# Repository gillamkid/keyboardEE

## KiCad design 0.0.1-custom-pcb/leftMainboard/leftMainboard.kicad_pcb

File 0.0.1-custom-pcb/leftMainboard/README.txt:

leftMainboard -- Glove80 LH controller, photograph reconstruction
KiCad 9 project, draft revision 1

OPEN
Open leftMainboard.kicad_pro in KiCad. Both an editable board and a four-sheet
schematic are included. Reconstruction.pretty and Reconstruction.kicad_sym
are project-local libraries. Your existing breakout projects were not edited.

STATUS AND SCOPE
This is a best-effort reconstruction of the photographed Rev J / 2022 board.
Component positions, four mounting holes, USB/GPIO/power/battery connectors,
FPC rows and the long matrix bus bundle follow the photos. Native F.Cu/B.Cu
routing represents the inferred netlist. Ambiguous paths were re-routed;
the native copper is an approximation, not a verified trace-for-trace clone.
Do not fabricate or energize this draft as a verified Glove80 replacement.

The photos do not establish all resistor/capacitor values, concealed connections,
board thickness/layer stack, every semiconductor MPN or connector polarity.
The power stage and LED interface require actual-board continuity checks and
identification of U1/Q1/Q2/Q3 before a working circuit can be claimed.
U1 BOOST_COMP and BOOST_SS are deliberately unresolved named terminals.
The final LED return IN40 is intentionally not connected to the processor.

LAYOUT GEOMETRY
Nominal size: 45 x 75 mm, estimated from known module dimensions and pitches.
Notch: approximately 7.5 x 25 mm. Holes: approximately 3 mm diameter.
Coordinates and dimensions were inferred from photos without a ruler; expect
roughly 0.5--1 mm placement/dimension uncertainty. Confirm the actual dimensions,
hole plating, screw clearance and enclosure fit before using the board mechanically.
Larger substitute footprints occasionally require small placement shifts.
The native routing uses 0.10 mm minimum clearance and some 0.10 mm escape tracks,
with 0.40/0.20 and 0.45/0.20 mm vias. These are reconstruction assumptions.
Some MCU escapes use vias in pads; the actual board's via process is unverified.
The rear ground fill and long front strap are photo-derived; additional top-side
ground areas and stitching connections are inferred to complete draft connectivity.

PHOTOGRAPH REFERENCES
references/Top.png: populated board, rectified to 30 pixels per mm.
references/TopSanded.png and BottomSanded.png: registered surface-copper photos.
The *-grid.png files add a 1 mm coordinate grid. Bottom images are registered
in the same top-view coordinate system as the KiCad PCB.
references/photo-registration.json records the homographies and mounting-hole landmarks.

User.1 (Photo top copper) and User.2 (Photo bottom copper) hold native graphical
copper-edge contours extracted from the photos. They are documentary graphics.
They do not represent electrical nets or contribute to fabrication copper.
Thresholding includes some sanding artifacts and misses obscured/shadowed copper;
the registered photographs retain the original evidence. Toggle these layers
individually to compare them against the editable F.Cu/B.Cu routing.
The battery envelope is on Dwgs.User; it is not an assembled PCB component.
Reference designators are on F.Fab to keep the densely packed silk uncluttered.

CONNECTORS -- REQUESTED USER PINOUTS
J7, 14 contacts, nearest the processor:
1 R0, 2 R1, 3 R2, 4 R3, 5 R4, 6 R5, 7 VDD, 8 GND,
9 IN16, 10 IN0, 11 C2, 12 C1, 13 C0, 14 NC. Anchors 15/16 NC.
J8, nearest 12-contact connector to J7:
1..6 R0..R5, 7 VDD, 8 GND, 9 IN22, 10 IN16, 11 C3, 12 NC.
J9, middle remaining 12-contact connector:
1..6 R0..R5, 7 VDD, 8 GND, 9 IN28, 10 IN22, 11 C4, 12 NC.
J10, farthest connector from J7:
1..6 R0..R5, 7 VDD, 8 GND, 9 IN40, 10 IN28, 11 C6, 12 C5.
All 12-contact mechanical anchors 13/14 are NC.
VDD denotes the external LED supply, estimated at 5 V, not the MCU 2.4 V rail.
FPC MPNs are substitutes from your breakout libraries, not identified factory parts.

FIRMWARE MAPPING -- CONFIRMED BY OFFICIAL DEVICE TREE
R0: P0.26
R1: P0.05
R2: P0.06
R3: P0.08
R4: P0.07
R5: P1.09
C0: P1.01
C1: P1.03
C2: P1.05
C3: P1.07
C4: P1.06
C5: P1.04
C6: P1.08
LED serial data: P0.27
LED power enable: P0.31
Rear status LED PWM: P1.15

The LH firmware array lists columns in the opposite order from your C0-at-thumb
numbering; the table above translates to your physical C0..C6 convention.
Each half has 40 LEDs. The inferred external chain follows 16 + 6 + 6 + 12 keys:
IN0 -> J7 breakout -> IN16 -> J8 -> IN22 -> J9 -> IN28 -> J10 -> IN40.

J3 GPIO/SWD header, 2 x 6, pitch 1.27 mm:
1 GND, 2 VEXT_2V4, 3 VDDH, 4 EXT1, 5 EXT2, 6 EXT3,
7 EXT4, 8 EXT5, 9 EXT6/SWO, 10 RESET, 11 SWDCLK, 12 SWDIO.
EXT1: P0.22
EXT2: P0.21
EXT3: P0.24
EXT4: P0.20
EXT5: P0.25
EXT6: P1.00
MoErgo documents VEXT as typically 2.4 V and VDDH as approximately 3--5 V.
RESET connects to module P0.18; SWDIO/SWDCLK use their dedicated module pads.

PARTS WITH THE STRONGEST EVIDENCE
U4: Raytac MDBT50Q nRF52840 module, PCB antenna variant; suffix P1MV2 inferred.
U2: TP4056 charger marking clearly visible; exact package/ordering suffix inferred.
U3: Nexperia PRTR5V0U2X USB protection, consistent with %R1 marking and SOT143.
L1: 330 marking supports 33 uH; current rating and exact MPN are unknown.
J3: official GPIO header and mapping, with photographed 1.27 mm pitch.

PARTS / DETAILS REQUIRING IDENTIFICATION OR MEASUREMENT
U1: unidentified eight-pin boost controller, marking resembles MXCEA/M1CEA.
The TPS61085-like functional pin map is only a provisional guess; no compatible
replacement or original pinout was established. Feedback/compensation/soft-start
and LED-enable behavior must be checked. Do not order U1 based on this guess.
U5: b25 marking suggests 74CBTLV1G125GV. That device is a 2.3--3.6 V bus switch;
it is not a generic 5 V buffer. The draft uses VEXT_2V4 for its supply, but the
photographed LED voltage-translation topology is unresolved.
Q1/Q3: N-channel MOSFETs supported by user diode measurements and SS marking;
BSS138 remains a candidate, with exact manufacturer/MPN unconfirmed.
Q2: user-selected TECH PUBLIC DMG2305UX, LCSC C2940629; P-channel confirmed by user multimeter test, 5PEY marking matches manufacturer 5Pxx format. Manually sized footprint pads retained.
D3/D4: likely Schottky diodes; BAT54WS and PMEG2010ER are estimates, not verified.
D5: status LED package/colour/current rating inferred.
F1: Bourns MF-NSMF150-2, LCSC C89655; 1.5 A hold, 3 A trip, 6 V, 1206 resettable fuse. Selected by user from the marking and measured package dimensions.
Y1: likely a 32.768 kHz crystal; load capacitance and exact package unverified.
L2/L3: ferrite/filter and 10 uH MCU power inductor estimates.
Every resistor/capacitor value, rating and package is inferred. Even apparently
standard 5.1k USB CC resistors should be confirmed on the actual board.
SW1: latching DPDT-style power switch; footprint and terminal assignment estimated.
SW2: user-selected SHOU HAN TS3735A 250gf 030, LCSC C2906282. Project-local EasyEDA footprint and STEP/VRML models. Common pairs 1/2 = RESET and 3/4 = GND; footprint rotated 90 degrees to preserve left/right net sides.
J1: generic 16-contact USB-C footprint; compare shell lands with the factory part.
J2: estimated 1.25 mm three-wire LiPo connector; verify family AND BATTERY POLARITY.
TP1..TP14: exposed small lands beside the column-filter components; their probing
function and inferred column/GND assignments are unconfirmed.
H1..H4: inferred plated holes, confirm whether the originals are plated.
See component-confidence.csv for the evidence and candidate for every footprint.

VALIDATION
review/ contains the final KiCad DRC and ERC reports, netlist export, board
previews and a schematic-to-PCB audit. Unresolved DRC findings are preserved.
The schematic symbols are evidence-capture symbols with passive electrical pins;
ERC cannot validate the assumed IC functions or prove that this circuit works.
Passing net/pin checks establishes consistency of the reconstruction only.

Evidence sources and the pinned firmware revision are in references/sources.txt.

FINAL CHECK RESULTS (KiCad 9.0.8, 2026-10-07)
300 physical pad instances checked against the inferred pin maps and schematic.
0 pin-map mismatches; 0 schematic/PCB parity issues; 0 unrouted connections.
8 DRC errors, all courtyard overlaps among estimated footprints.
20 DRC warnings: unused track/via ends remain in the reconstructed buses.
0 ERC errors; 4 singleton global-label warnings (IN40, BOOST_COMP, BOOST_SS, CHARGE_DONE).
The latter reflect an unused final LED return and unresolved/unused power-stage terminals.
Detailed counts and component pairs are in review/drc.rpt and schematic-pcb-audit.json.
These checks establish internal net consistency, not a verified working circuit.

PROJECT-LOCAL 3D MODELS
All 60 fitted component footprints now have local 3D models under 3dmodels/.
Model assignments are updated in the PCB and Reconstruction.pretty library.
SW1, SW2 and L1 now use project-local EasyEDA models for their selected parts;
J2 and Y1 use representative library models for the estimated package.
See 3dmodels/README.txt and review/3d-model-coverage.csv for provenance and limits.

EMBEDDED SANDED-BOARD PHOTOGRAPHS 20261007-185202
Actual full-color PNG photos are embedded directly in the PCB, at registered 45x75mm size. User.3: Sanded top photo. User.4: Sanded bottom photo (registered to the same top-view coordinates). Select one of these layers in the PCB Editor Appearance panel; show one photo at a time. User.1/User.2 remain the earlier copper contour references. Images are locked against accidental movement. Local view preferences show the top photo at full opacity and hide the other photo and contour layers. Board copper, pads, component placements, models and connections were preserved. See review/embedded-sanded-photos.json.

REFERENCE LAYER CLEANUP 20261007-213601
Removed Photo top copper (User.1) and Photo bottom copper (User.2) and their 6877 obsolete contour graphics from this PCB. Sanded top/bottom photos on User.3/User.4 remain embedded and locked. Photo centers realigned to [72.36667, 87.63333] mm, following the board translation [49.86667, 50.13333] mm measured from all four mounting holes. Earlier notes describing the contour layers and fixed origin are superseded. Existing copper, pads, holes, component positions and 3D models were preserved exactly.

L1 REPLACEMENT 20261008-135743
Left mainboard L1 now uses user-selected XRCD54-1R8M / LCSC C5339378, 1.8uH +/-20%, 4A, DCR 30mOhm max. This supersedes the former photo-estimated 33uH value. The schematic, PCB, local footprint and local symbol defaults have been updated; pin 1 remains VDDH and pin 2 BOOST_SW. Position is unchanged; the footprint angle is now 90 degrees to preserve the upper/lower net arrangement with EasyEDA native pad numbering. Source pad positions +/-2.33mm and sizes 3x5.5mm imported; body contour is F.Fab and a bounding courtyard enclosing pads has been added. Both STEP and colored VRML are stored inside this project; STEP is active. User explicitly requested leaving all tracks and vias unchanged, so connections/DRC are not repaired. Original part identification and suitability for unidentified U1 remain unverified.

Q1/Q3 N-CHANNEL IDENTIFICATION 20261009-115006
Q1 diode display 414 (~0.414 V), Q3 440 (~0.440 V), gate/source pins 1/2 shorted, red on source 2 and black on drain 3. Both bear SS and measure about 3x1.3 mm. Q3 is changed from a P-channel guess to a BSS138 N-channel candidate; Q1 identification is reinforced. Schematic pin names are G/S/D for 1/2/3. Exact manufacturer/MPN remains unconfirmed; no LCSC ordering number was assigned from these readings. Measurements were not reported as isolated-device tests and no reverse reading was supplied. Existing nets, routing, placement and models were preserved. Q3 source remains on the inferred VEXT_2V4 connection, which requires separate continuity verification against the original board; this part identification does not validate that connection.

Q1/Q3 SELECTED PART AND MODEL 20261009-121635
Both Q1 and Q3 now use user-selected LCSC C7420339, R+O BSS138. Component values are BSS138 N-channel with the candidate suffix removed. Schematic, PCB and local library LCSC fields match. Project-local EasyEDA STEP and VRML imported; native 3D model is shared with other SOT-23 parts and does not verify original manufacturer or circuit connectivity. Routing, pads and positions preserved.

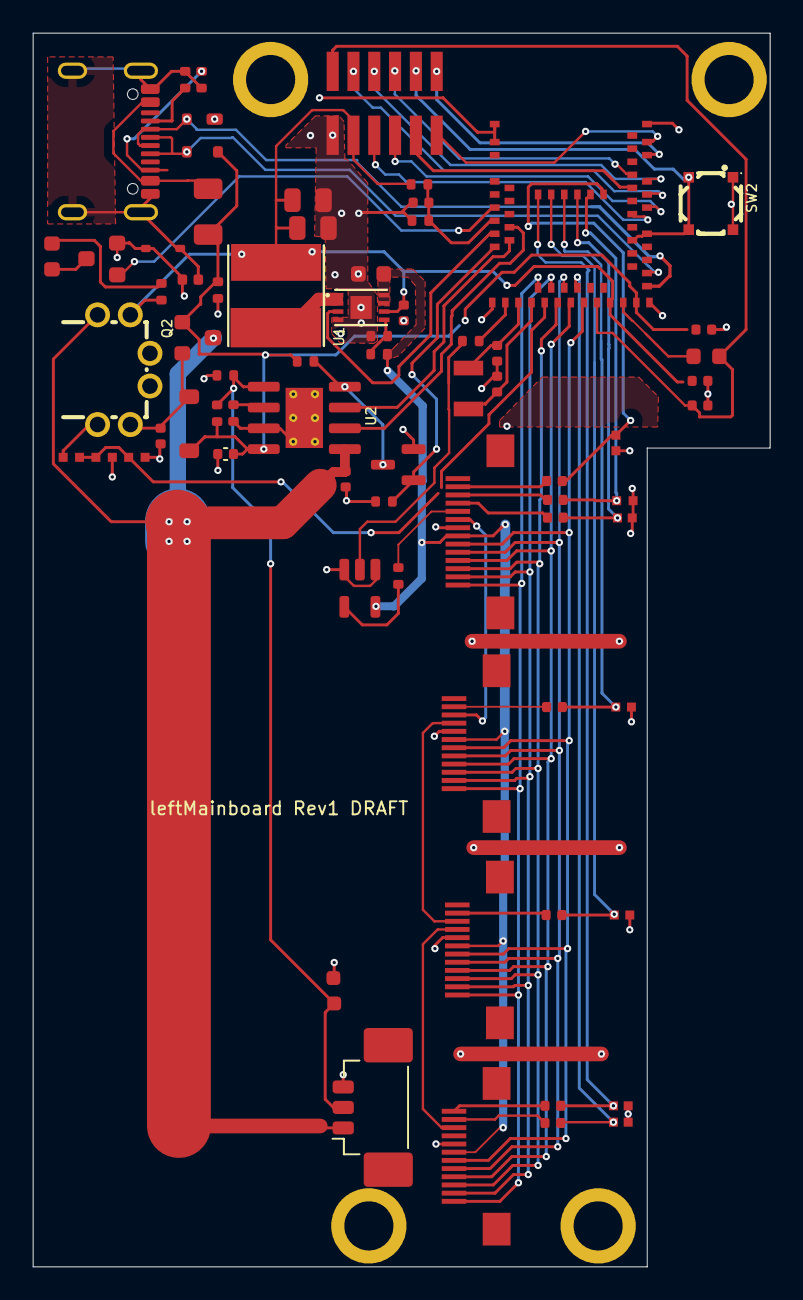
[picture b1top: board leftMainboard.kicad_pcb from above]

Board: 2 copper layers, 45.0 x 75.3 mm, 79 parts (0 on the bottom side), 53 nets.

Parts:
C1: 10uF; C1_C_0805_2012Metric
C2: 1uF; C2_C2_C_0402_1005Metric
C3: 100nF; C3_C_0402_1005Metric
C4: 10uF; C4_C_0603_1608Metric
C5: 100nF; C5_C_0402_1005Metric
C6: 100nF; C6_C_0402_1005Metric
C7: 100nF; C7_C_0402_1005Metric
C8: 12pF; C8_C_0402_1005Metric
C9: 12pF; C9_C_0402_1005Metric
C10: 1uF; C10_C_0402_1005Metric
C11: 1uF; C11_C_0402_1005Metric
C12: 100nF; C12_C_0402_1005Metric
C13: 100pF; C13_C_0402_1005Metric
C14: 100pF; C14_C_0402_1005Metric
C15: 100pF; C15_C_0402_1005Metric
C16: 100pF; C16_C_0402_1005Metric
C17: 100pF; C17_C_0402_1005Metric
C18: 100pF; C18_C_0402_1005Metric
C19: 100pF; C19_C_0402_1005Metric
C20: 10uF; C20_C_0805_2012Metric
D3: BAT54WS (guess); D3_D_SOD-323
D4: PMEG2010ER (guess); D4_D_SOD-123
D5: Green status LED (guess); D5_LED_0603_1608Metric
F1: MF-NSMF150-2; F1_Fuse_1206_3216Metric
H1, H2, H3, H4: 3mm mounting hole (estimate); MountingHole_3mm_PhotoEstimate
J1: USB-C USB2 receptacle (footprint estimate); J1_USB_C_Receptacle_GCT_USB4105-xx-A_16P_TopMnt_Horizontal
J2: 53398-0371; J_Molex_53398_0371_C293633
J3: GPIO / SWD 2x6 1.27mm; PinHeader_2x06_P1.27mm_Vertical_SMD
J7: HC-FPC-0.5-14P-FH20; FPC-SMD_14P-P0.50_HC-FPC-0.5-14P-FH20
J8, J9, J10: HC-FPC-0.5-12P-FH20; FPC-SMD_12P-P0.50_HC-FPC-0.5-12P-FH20
L1: 1.8uH; L_XRCD54_5.8x5.2mm_C5339378
L2: Ferrite bead (guess); L2_L_0402_1005Metric
L3: 10uH (guess); L3_L_0603_1608Metric
Q1: BSS138 N-channel; Q1_SOT-23
Q2: DMG2305UX; Q2_SOT-23
Q3: BSS138 N-channel; Q3_SOT-23
R1: 30.1k; R1_R_0402_1005Metric
R2: 10k; R2_R_0402_1005Metric
R3: 5.1k; R3_R_0402_1005Metric
R4: 5.1k; R4_R_0402_1005Metric
R5: 10k; R5_R_0402_1005Metric
R6: 10k; R6_R_0402_1005Metric
R7: 12k; R7_R_0402_1005Metric
R8: 0R; R8_R_0402_1005Metric
R9: 100k; R9_R_0402_1005Metric
R10: 330R; R10_R_0402_1005Metric
R11: 100k; R11_R_0402_1005Metric
R12: 1k; R12_R_0402_1005Metric
R13: 10k; R13_R_0402_1005Metric
R14: 1M; R14_R_0402_1005Metric
R22: 100k; R22_R_0402_1005Metric
SW1: TK-6580A-1; SW_TK6580A1_C528770
SW2: TS3735A 250gf 030; SW_TS3735A_C2906282_EasyEDA
TP1: C0 exposed pad; TestPad_0.55mm
TP2, TP4, TP6, TP8, TP10, TP12, TP14: GND exposed pad; TestPad_0.55mm
TP3: C1 exposed pad; TestPad_0.55mm
TP5: C2 exposed pad; TestPad_0.55mm
TP7: C3 exposed pad; TestPad_0.55mm
TP9: C4 exposed pad; TestPad_0.55mm
TP11, TP11#2: C5 exposed pad; TestPad_0.55mm
TP13: C6 exposed pad; TestPad_0.55mm
U1: SY7088DGC; DFN8_SY7088DGC_2x3mm_C178240
U2: TP4056-42-ESOP8; U2_SOIC-8-1EP_3.9x4.9mm_P1.27mm_EP2.29x3mm_ThermalVias
U3: PRTR5V0U2X; U3_SOT-143
U4: MDBT50Q-P1MV2; Raytac_MDBT50Q
U5: 74CBTLV1G125GV (probable b25 marking); U5_SOT-23-5
Y1: 32.768kHz (guess); Crystal_3215_2pin_PhotoEstimate

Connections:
BAT_NTC: J2.2, R5.2, R6.1, TP11#2.1, U2.1
BOOST_FB: R1.2, R2.1, U1.5
BOOST_SW: L1.2, U1.1, U1.2
C0: C13.1, C13.2, J7.13, TP1.1, U4.61
C1: C14.1, C14.2, J7.12, TP3.1, U4.60
C2: C15.1, C15.2, J7.11, TP5.1, U4.59
C3: C16.1, C16.2, J8.11, TP7.1, U4.58
C4: C17.1, C17.2, J9.11, TP9.1, U4.57
C5: C18.1, C18.2, J10.12, TP11.1, U4.56
C6: C19.1, C19.2, J10.11, TP13.1, U4.25
CC1: J1.A5, R3.1
CC2: J1.B5, R4.1
CHARGE_DONE: U2.6, U4.11
CHARGE_PROG: R7.1, U2.2
CHARGING: U2.7, U4.13
DCCH: L3.1, U4.31
EXT1: J3.4, U4.46
EXT2: J3.5, U4.43
EXT3: J3.6, U4.48
EXT4: J3.7, U4.44
EXT5: J3.8, U4.49
EXT6: J3.9, U4.47
GND: C1.1, C2.1, C3.1, C4.1, C5.1, C6.1, C7.1, C8.1, C9.1, C10.1, C11.1, C12.1, C20.1, D3.1, D3.2, J1.A1, J1.A12, J1.B1, J1.B12, J1.S1, J2.3, J3.1, J7.8, J8.8, J9.8, J10.8, L2.1, L2.2, Q1.2, Q3.2, R2.2, R3.2, R4.2, R6.2, R7.2, R11.2, R14.1, R22.2, SW2.1, SW2.2, TP2.1, TP4.1, TP6.1, TP8.1, TP10.1, TP12.1, TP14.1, U1.4, U1.9, U2.3, U2.9, U3.1, U4.1, U4.2, U4.15, U4.33, U4.55, U5.1, U5.3
IN0: J7.10, R10.2
IN16: J7.9, J8.10
IN22: J8.9, J9.10
IN28: J9.9, J10.10
LED_DATA_5V: R10.1, U5.4
LED_DATA_MCU: R8.1, R8.2, U4.16, U5.2
LED_ENABLE: Q1.1, R22.L, U1.3, U4.12, U4.14
R0: J7.1, J8.1, J9.1, J10.1, U4.19
R1: J7.2, J8.2, J9.2, J10.2, U4.21
R2: J7.3, J8.3, J9.3, J10.3, U4.22
R3: J7.4, J8.4, J9.4, J10.4, U4.24
R4: J7.5, J8.5, J9.5, J10.5, U4.23
R5: J7.6, J8.6, J9.6, J10.6, U4.26
REAR_LED_ANODE: D5.2, R12.2
REAR_LED_PWM: Q3.1, U4.8
REAR_LED_SUPPLY: D5.1, Q3.3
RESET: J3.10, SW2.3, SW2.4, U4.40, U4.41
SW1_ON_VDDH: C6.2, D4.1, Q2.2, SW1.2
SWDCLK: J3.11, U4.53
SWDIO: J3.12, U4.51
USB_D+: J1.A6, J1.B6, U3.3, U4.35
USB_D-: J1.A7, J1.B7, U3.2, U4.34
VBAT: J2.1, Q2.3, SW1.3, U2.5
VBUS_FUSED: C2.2, C5.2, D4.2, F1.2, Q1.3, Q2.1, R5.1, R9.1, R9.2, R11.1, U2.4, U2.8, U3.4
VBUS_USB: F1.1, J1.A4, J1.A9, J1.B4, J1.B9, U4.32
VDD: C4.2, J7.7, J8.7, J9.7, J10.7, R1.1, U1.7, U1.8, U5.5
VDDH: C1.2, C3.2, C20.2, J3.3, L1.1, R12.1, R13.1, SW1.4, U1.6, U4.30
VEXT_2V4: C11.2, C12.2, J3.2, L3.2, U4.28
XL1: C9.2, U4.17, Y1.2
XL2: C8.2, U4.18, Y1.1

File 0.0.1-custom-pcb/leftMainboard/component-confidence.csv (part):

Reference,Value / guess,Candidate MPN,Confidence,Evidence,X mm,Y mm,Rotation,DNP
H1,3mm mounting hole (estimate),,Medium,Four visible holes; diameter inferred from photo scale,14.5,2.5,0.0,False
H2,3mm mounting hole (estimate),,Medium,Four visible holes; diameter inferred from photo scale,42.5,2.5,0.0,False
H3,3mm mounting hole (estimate),,Medium,Four visible holes; diameter inferred from photo scale,20.5,72.5,0.0,False
H4,3mm mounting hole (estimate),,Medium,Four visible holes; diameter inferred from photo scale,34.5,72.5,0.0,False
U4,MDBT50Q-P1MV2,,High,Raytac MDBT50Q shield marking + PCB antenna; nRF52840 firmware; exact module suffix inferred,32.8,8.6,0.0,False
J7,HC-FPC-0.5-14P-FH20,C19273929,"High (pinout), Medium (MPN)",Pinout copied from user breakout PCB; connector locations from photo; housing substitute,27.0,29.95,90.0,False
J8,HC-FPC-0.5-12P-FH20,C19273928,"High (pinout), Medium (MPN)",Pinout copied from user breakout PCB; connector locations from photo; housing substitute,27.0,43.05,90.0,False
J9,HC-FPC-0.5-12P-FH20,C19273928,"High (pinout), Medium (MPN)",Pinout copied from user breakout PCB; connector locations from photo; housing substitute,27.0,55.05,90.0,False
J10,HC-FPC-0.5-12P-FH20,C19273928,"High (pinout), Medium (MPN)",Pinout copied from user breakout PCB; connector locations from photo; housing substitute,27.0,68.25,90.0,False
J1,USB-C USB2 receptacle (footprint estimate),GCT USB4105-GF-A,Medium,"16 contacts, four shell anchors visible; connector mounted facing board side",4.2,6.15,-90.0,False
J2,53398-0371,C293633 / 53398-0371,User-selected replacement; original part unconfirmed,User-selected C293633 replacement; Molex PicoBlade 53398-0371 vertical 3-pin 1.25 mm SMT; exact-part KiCad footprint and detailed EasyEDA model,20.15,65.2,180.0,False
J3,GPIO / SWD 2x6 1.27mm,,High,Official MoErgo header schematic and GPIO mapping,21.95,3.5,90.0,False
SW2,Reset tactile 4x4mm (estimate),4x4mm SMT tactile switch,User-selected replacement; original part unconfirmed,User-selected C2906282; footprint and 3D models imported from JLCEDA/EasyEDA Official Library; common pin pairs 1/2 and 3/4 checked against manufacturer drawing,42.45,9.75,90.0,False
SW1,TK-6580A-1,C528770 / TK-6580A-1,User-selected replacement; original part unconfirmed,User-selected replacement; footprint and models from JLCEDA/EasyEDA Official Library; pin function checked against manufacturer drawing,4.8,19.4,0.0,False
U1,SY7088DGC,C178240 / SY7088DGC,High: marking and body size match; selected replacement,User-reported VTGEA marking and approximately 2.1x3 mm body match Silergy VTxyz marking and DFN2x3-8; selected C178240; pinout checked against manufacturer datasheet,21.2,16.4,-90.0,False
U2,TP4056-42-ESOP8,,"High (family), Medium (variant)",TP4056 marking visible; exposed pad visible in sanded board. Exact suffix unconfirmed,15.6,22.8,180.0,False
U3,PRTR5V0U2X,,High,WR1 marking and four-lead SOT143 match manufacturer %R1 code,10.7,5.6,90.0,False
U5,74CBTLV1G125GV (probable b25 marking),74CBTLV1G125GV; surrounding topology unverified,"Medium (marking), Low (circuit)",b25 marking matches Nexperia bus switch; uses 2.4V rail. Exact surrounding LED translation circuit unresolved.,20.6,32.4,180.0,False
Q1,BSS138 N-channel,BSS138; selected LCSC C7420339,Medium,"User measured body about 3x1.3 mm, marking SS; diode-mode display 414 (about 0.414 V), pins 1/2 shorted, red 2 black 3; supports N-channel; reverse reading and isolated-device test not reported; exact MPN unconfirmed",22.5,25.3,180.0,False
Q2,DMG2305UX,C2940629 / DMG2305UX,User-selected replacement; P-channel confirmed by user,User confirmed P-channel by multimeter; reported 5PEY marking matches manufacturer 5Pxx marking format; user-selected C2940629,10.45,17.9,180.0,False
Q3,BSS138 N-channel,BSS138; selected LCSC C7420339,Medium,"User measured body about 3x1.3 mm, marking SS; diode-mode display 440 (about 0.440 V), pins 1/2 shorted, red 2 black 3; supports N-channel; reverse reading and isolated-device test not reported; exact MPN unconfirmed",4.5,13.7,180.0,False
R1,30.1k,,Low,0402 package estimated; resistance not readable,19.6,19.9,0.0,False
R2,10k,,Low,0402 package estimated; resistance not readable,21.7,20.0,0.0,False
R3,5.1k,,Medium (5.1k inferred),0402 package estimated; resistance not readable,9.4,2.0,90.0,False
R4,5.1k,,Medium (5.1k inferred),0402 package estimated; resistance not readable,10.9,2.0,0.0,False
R5,10k,,Low,0402 package estimated; resistance not readable,10.9,22.5,0.0,False
R6,10k,,Low,0402 package estimated; resistance not readable,10.9,23.3,0.0,False
R7,12k,,Low,0402 package estimated; resistance not readable,10.9,21.0,0.0,False
R8,0R,,Low,0402 package estimated; resistance not readable,25.6,17.9,0.0,False
R9,100k,,Low,0402 package estimated; resistance not readable,21.2,22.0,0.0,False
R10,330R,,Low,0402 package estimated; resistance not readable,23.8,32.5,90.0,False
R11,100k,,Low,0402 package estimated; resistance not readable,9.7,14.45,90.0,False
R12,1k,,Low,0402 package estimated; resistance not readable,7.8,15.15,0.0,False
R13,10k,,Low,0402 package estimated; resistance not readable,23.5,8.65,0.0,False
R14,1M,,Low,0402 package estimated; resistance not readable,23.5,10.8,0.0,False
R22,100k,,Low,0402 package estimated; resistance not readable,19.7,27.6,90.0,False
C1,10uF,,Low,Ceramic capacitor values and voltage ratings are not readable; estimated from function/package,17.1,9.5,0.0,False
C2,1uF,,Low,Ceramic capacitor values and voltage ratings are not readable; estimated from function/package,11.2,25.0,0.0,False
C3,100nF,,Low,Ceramic capacitor values and voltage ratings are not readable; estimated from function/package,23.6,16.5,90.0,False
C4,10uF,,Low,Ceramic capacitor values and voltage ratings are not readable; estimated from function/package,20.9,12.7,0.0,False
C5,100nF,,Low,Ceramic capacitor values and voltage ratings are not readable; estimated from function/package,8.4,26.5,0.0,False
C6,100nF,,Low,Ceramic capacitor values and voltage ratings are not readable; estimated from function/package,6.4,26.5,0.0,False
C7,100nF,,Low,Ceramic capacitor values and voltage ratings are not readable; estimated from function/package,23.5,9.7,0.0,False
C8,12pF,,Low,Ceramic capacitor values and voltage ratings are not readable; estimated from function/package,28.4,20.4,0.0,False
C9,12pF,,Low,Ceramic capacitor values and voltage ratings are not readable; estimated from function/package,28.7,19.3,0.0,False
C10,1uF,,Low,Ceramic capacitor values and voltage ratings are not readable; estimated from function/package,40.4,17.3,0.0,False
C11,1uF,,Low,Ceramic capacitor values and voltage ratings are not readable; estimated from function/package,40.4,20.3,0.0,False
C12,100nF,,Low,Ceramic capacitor values and voltage ratings are not readable; estimated from function/package,40.4,21.7,0.0,False
C13,100pF,,Low,Ceramic capacitor values and voltage ratings are not readable; estimated from function/package,32.7,27.25,0.0,False
TP1,C0 exposed pad,,Low,Exposed pads seen in photo; function inferred as probing pads,36.0,27.25,0.0,False
TP2,GND exposed pad,,Low,Exposed pads seen in photo; function inferred as probing pads,35.1,27.25,0.0,False
C14,100pF,,Low,Ceramic capacitor values and voltage ratings are not readable; estimated from function/package,32.7,28.25,0.0,False
TP3,C1 exposed pad,,Low,Exposed pads seen in photo; function inferred as probing pads,36.0,28.25,0.0,False
TP4,GND exposed pad,,Low,Exposed pads seen in photo; function inferred as probing pads,35.1,28.25,0.0,False
C15,100pF,,Low,Ceramic capacitor values and voltage ratings are not readable; estimated from function/package,32.7,29.25,0.0,False
TP5,C2 exposed pad,,Low,Exposed pads seen in photo; function inferred as probing pads,36.0,29.25,0.0,False
TP6,GND exposed pad,,Low,Exposed pads seen in photo; function inferred as probing pads,35.1,29.25,0.0,False
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
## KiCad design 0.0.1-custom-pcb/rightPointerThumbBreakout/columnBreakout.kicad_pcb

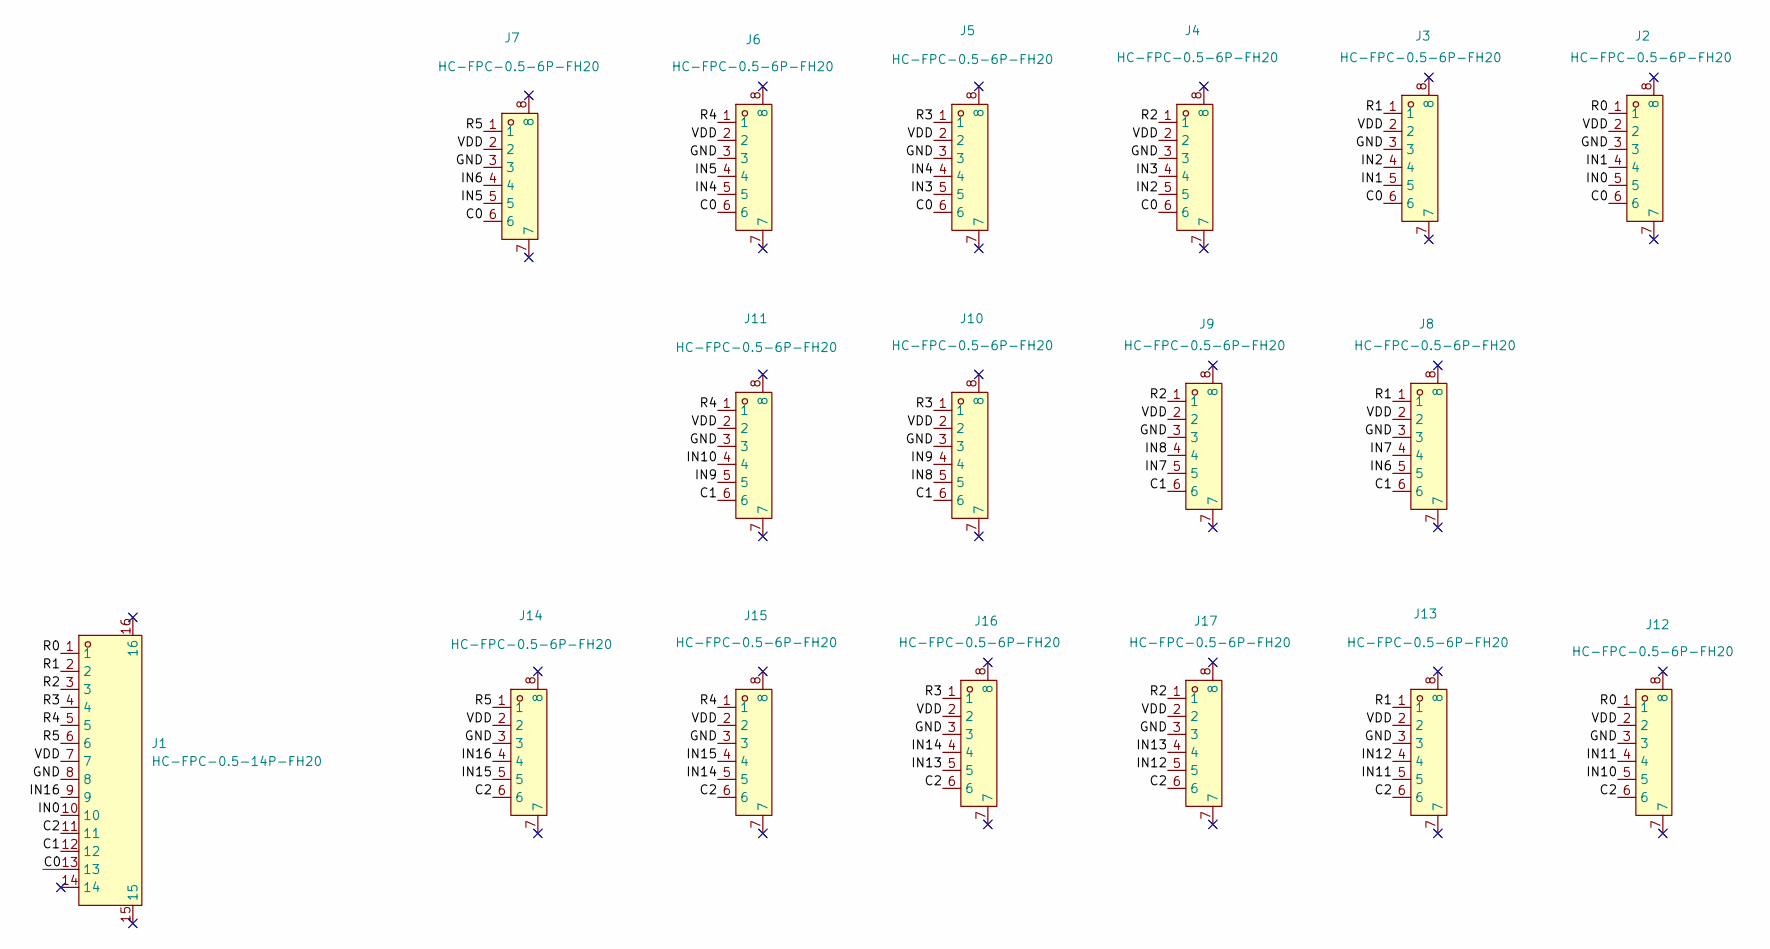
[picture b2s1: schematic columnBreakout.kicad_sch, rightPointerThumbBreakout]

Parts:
J1: HC-FPC-0.5-14P-FH20; FPC-SMD_14P-P0.50_HC-FPC-0.5-14P-FH20; MPN HC-FPC-0.5-14P-FH20; LCSC Part C19273929
J2, J3, J4, J5, J6, J7, J8, J9, J10, J11, J12, J13, J14, J15, J16, J17: HC-FPC-0.5-6P-FH20; FPC-SMD_6P-P0.50_HC-FPC-0.5-6P-FH20; MPN HC-FPC-0.5-6P-FH20; LCSC Part C19273925

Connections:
/C0: J1.13, J2.6, J3.6, J4.6, J5.6, J6.6, J7.6
/C1: J1.12, J8.6, J9.6, J10.6, J11.6
/C2: J1.11, J12.6, J13.6, J14.6, J15.6, J16.6, J17.6
/GND: J1.8, J2.3, J3.3, J4.3, J5.3, J6.3, J7.3, J8.3, J9.3, J10.3, J11.3, J12.3, J13.3, J14.3, J15.3, J16.3, J17.3
/IN0: J1.10, J2.5
/IN1: J2.4, J3.5
/IN2: J3.4, J4.5
/IN3: J4.4, J5.5
/IN4: J5.4, J6.5
/IN5: J6.4, J7.5
/IN6: J7.4, J8.5
/IN7: J8.4, J9.5
/IN8: J9.4, J10.5
/IN9: J10.4, J11.5
/IN10: J11.4, J12.5
/IN11: J12.4, J13.5
/IN12: J13.4, J17.5
/IN13: J16.5, J17.4
/IN14: J15.5, J16.4
/IN15: J14.5, J15.4
/IN16: J1.9, J14.4
/R0: J1.1, J2.1, J12.1
/R1: J1.2, J3.1, J8.1, J13.1
/R2: J1.3, J4.1, J9.1, J17.1
/R3: J1.4, J5.1, J10.1, J16.1
/R4: J1.5, J6.1, J11.1, J15.1
/R5: J1.6, J7.1, J14.1
/VDD: J1.7, J2.2, J3.2, J4.2, J5.2, J6.2, J7.2, J8.2, J9.2, J10.2, J11.2, J12.2, J13.2, J14.2, J15.2, J16.2, J17.2

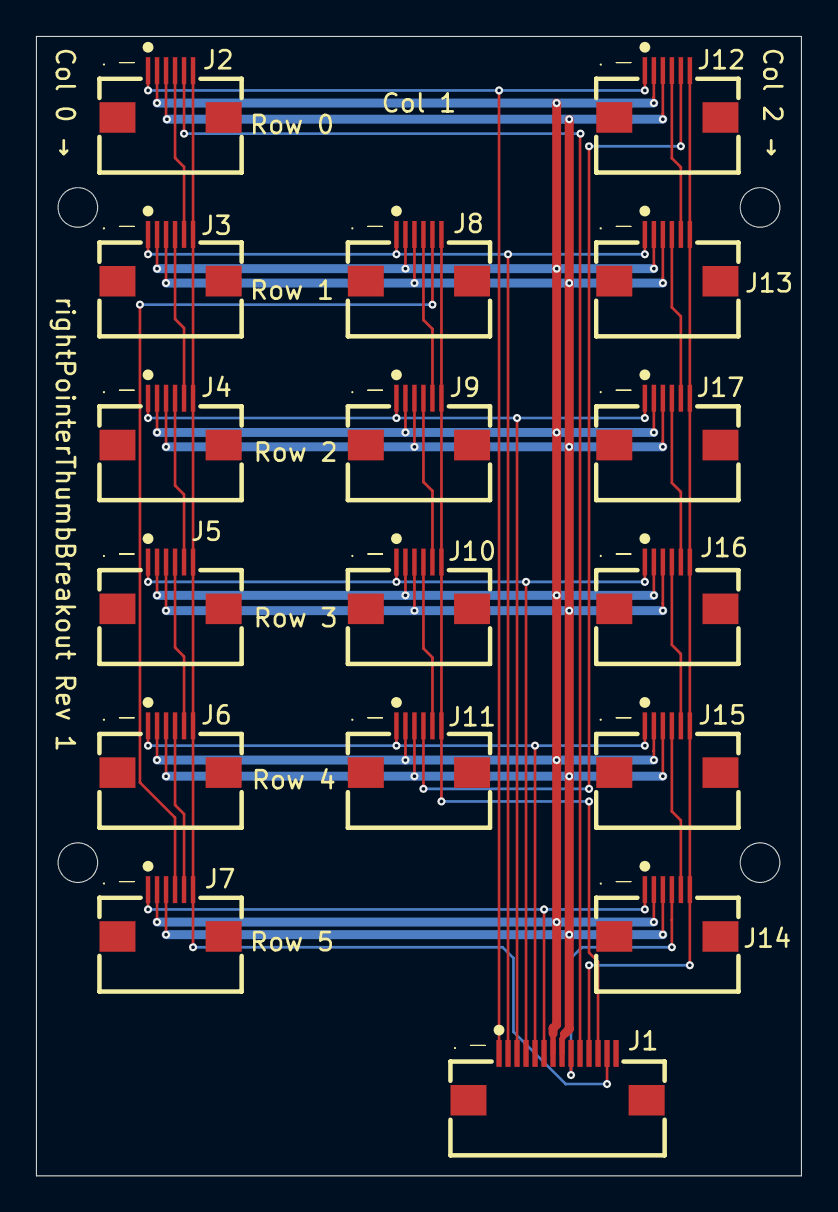
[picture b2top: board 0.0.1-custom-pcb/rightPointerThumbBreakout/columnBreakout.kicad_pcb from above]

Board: 2 copper layers, 42.5 x 63.3 mm, 21 parts (0 on the bottom side), 28 nets.

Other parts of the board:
H1, H2, H3, H4: MountingHole_2.2mm_M2_4.4mmHead

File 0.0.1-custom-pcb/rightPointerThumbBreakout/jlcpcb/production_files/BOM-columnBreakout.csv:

Comment,Designator,Footprint,LCSC,Quantity
HC-FPC-0.5-14P-FH20,J1,FPC-SMD_14P-P0.50_HC-FPC-0.5-14P-FH20,C19273929,1
HC-FPC-0.5-6P-FH20,"J10,J11,J12,J13,J14,J15,J16,J17,J2,J3,J4,J5,J6,J7,J8,J9",FPC-SMD_6P-P0.50_HC-FPC-0.5-6P-FH20,C19273925,16

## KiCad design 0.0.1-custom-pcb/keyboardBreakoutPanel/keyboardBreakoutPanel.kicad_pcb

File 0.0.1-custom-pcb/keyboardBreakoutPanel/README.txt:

keyboardBreakoutPanel Rev 1 — JLCPCB ordering files

Open keyboardBreakoutPanel.kicad_pro in KiCad. The PCB is a 152.4 x 73.3 mm
V-scored panel with one copy of each of the four breakout boards, a combined
four-sheet schematic, 5 mm handling rails, 3 tooling holes and 3 top fiducials.
The four source projects are unchanged. Connector geometry, electrical pin
assignments, traces, vias and drill sizes are preserved under translation.

Files to upload:
  manufacturing/gerber.zip — fabrication layers, drill files, V-CUT guide, notes
  manufacturing/bom.csv    — complete panel bill of materials, 60 connectors
  manufacturing/cpl.csv    — complete panel placements, TOP only

JLCPCB order settings:
  Delivery Format: Panel by Customer
  Panel array: 1 row x 4 columns, four different designs, unequal column widths
  Panel size: 152.4 x 73.3 mm; 2 layers; 1.6 mm FR4
  PCB Assembly: Standard Assembly, top side
  BOM/CPL file type: "Complete File, just proceed with my own files"
  V-score lines and handling rails: already included; use attached V-CUT guide
  Do not add another array or replicate these complete-panel BOM/CPL files.
  PCB quantity is panel quantity: N panels gives N copies of EACH board,
  or 4N individual subboards total. Leave rails attached through assembly.

Paste into fabrication remarks:
  Four different breakout PCBs in a 1 x 4 customer panel, 152.4 x 73.3 mm.
  Double-sided V-score along all seven full-span lines in V-CUT.gbr.
  Do not route the V-CUT lines; retain 5 mm rails during top-side assembly.
  BOM/CPL already contain all 60 panel components; no data replication.

Before confirming the JLCPCB order, check selected C-codes, stock availability,
all 60 placements/rotations, and the factory V-score engineering preview.

Validation:
  PCB DRC: 0 reported violations, 0 unconnected items, 0 schematic parity issues.
  Schematic ERC: 0 violations.
  Conservative minimum copper-to-V-score centerline clearance: 0.65 mm.
  Minimum NPTH edge-to-score centerline clearance: 1.20 mm.
  BOM/CPL references, quantities and shared Gerber/drill/CPL origin verified.
  All source PCB/schematic/project hashes verified unchanged.
  Detailed evidence: manufacturing/validation.txt, drc.rpt and erc.rpt.

Panel-specific courtyard rule:
  Six pairs of original mounting-hole screw-head courtyards overlap across
  subboard boundaries. These holes are not populated by JLCPCB, and screws
  are installed after boards are separated. keyboardBreakoutPanel.kicad_dru
  ignores ONLY the courtyard check for those six specific cross-board pairs.
  Assembly-component courtyard checks and copper/drill clearances remain active.
  Native rule areas prohibit copper within 0.4 mm of every V-score centerline.

Reference names:
  PCB/schematic/BOM/CPL use unique panel refs J1-J60.
  Original local J references remain on each board's silkscreen for familiar
  identification; reference-map.csv gives the exact mapping.
  LPK = leftPinkieBreakout (J1-J13)
  LPT = leftPointerThumbBreakout (J14-J30)
  RPT = rightPointerThumbBreakout (J31-J47)
  RPK = rightPinkieBreakout (J48-J60)
  Serial placeholders remain horizontal on bottom silkscreen and clear of
  traces. The left pointer's inherited placeholder was moved in this panel.

Preview files:
  manufacturing/panel-routing.png / .svg — copper and V-score overview
  manufacturing/panel-top.png — rendered components; V-scores are mechanical
  drawing metadata and do not appear as physical grooves in KiCad 3D rendering.
  manufacturing/panel-drawing.pdf / .svg — fabrication dimensions and score map

Official JLCPCB requirements consulted 2026-10-06:
  https://jlcpcb.com/help/article/pcb-panelization
  https://jlcpcb.com/capabilities/Capabilities?type=1
  https://jlcpcb.com/help/article/how-to-add-edge-rails-fiducials-for-pcb-assembly-order
  https://jlcpcb.com/help/article/common-bom-and-cpl-matching-issues-and-explanations

Source snapshots are frozen build inputs; the original sibling projects remain
available for editing. The panel is a snapshot and does not update automatically
when a source board changes.

Optional rebuild scripts: manufacturing/build-panel.py requires KiCad pcbnew and
sexpdata (available here with PYTHONPATH=/tmp/chocpcb-python). After rebuilding,
run export-jlcpcb.py and validate-panel.py, rerun DRC/ERC, and refresh previews.

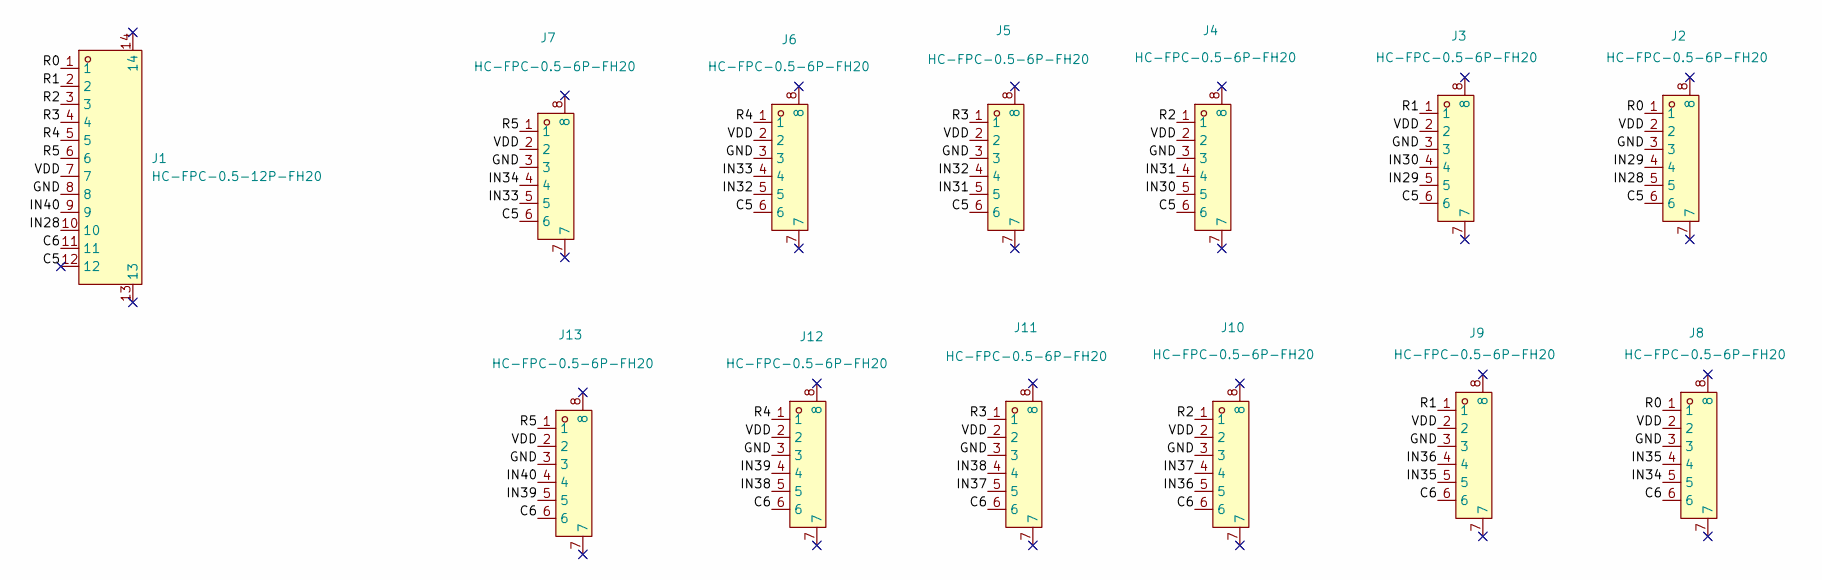
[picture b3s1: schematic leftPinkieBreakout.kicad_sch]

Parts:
J1: HC-FPC-0.5-12P-FH20; FPC-SMD_12P-P0.50_HC-FPC-0.5-12P-FH20; MPN HC-FPC-0.5-12P-FH20; LCSC Part C19273928
J2, J3, J4, J5, J6, J7, J8, J9, J10, J11, J12, J13: HC-FPC-0.5-6P-FH20; FPC-SMD_6P-P0.50_HC-FPC-0.5-6P-FH20; MPN HC-FPC-0.5-6P-FH20; LCSC Part C19273925

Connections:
/leftPinkieBreakout/C5: J1.12, J2.6, J3.6, J4.6, J5.6, J6.6, J7.6
/leftPinkieBreakout/C6: J1.11, J8.6, J9.6, J10.6, J11.6, J12.6, J13.6
/leftPinkieBreakout/GND: J1.8, J2.3, J3.3, J4.3, J5.3, J6.3, J7.3, J8.3, J9.3, J10.3, J11.3, J12.3, J13.3
/leftPinkieBreakout/IN28: J1.10, J2.5
/leftPinkieBreakout/IN29: J2.4, J3.5
/leftPinkieBreakout/IN30: J3.4, J4.5
/leftPinkieBreakout/IN31: J4.4, J5.5
/leftPinkieBreakout/IN32: J5.4, J6.5
/leftPinkieBreakout/IN33: J6.4, J7.5
/leftPinkieBreakout/IN34: J7.4, J8.5
/leftPinkieBreakout/IN35: J8.4, J9.5
/leftPinkieBreakout/IN36: J9.4, J10.5
/leftPinkieBreakout/IN37: J10.4, J11.5
/leftPinkieBreakout/IN38: J11.4, J12.5
/leftPinkieBreakout/IN39: J12.4, J13.5
/leftPinkieBreakout/IN40: J1.9, J13.4
/leftPinkieBreakout/R0: J1.1, J2.1, J8.1
/leftPinkieBreakout/R1: J1.2, J3.1, J9.1
/leftPinkieBreakout/R2: J1.3, J4.1, J10.1
/leftPinkieBreakout/R3: J1.4, J5.1, J11.1
/leftPinkieBreakout/R4: J1.5, J6.1, J12.1
/leftPinkieBreakout/R5: J1.6, J7.1, J13.1
/leftPinkieBreakout/VDD: J1.7, J2.2, J3.2, J4.2, J5.2, J6.2, J7.2, J8.2, J9.2, J10.2, J11.2, J12.2, J13.2

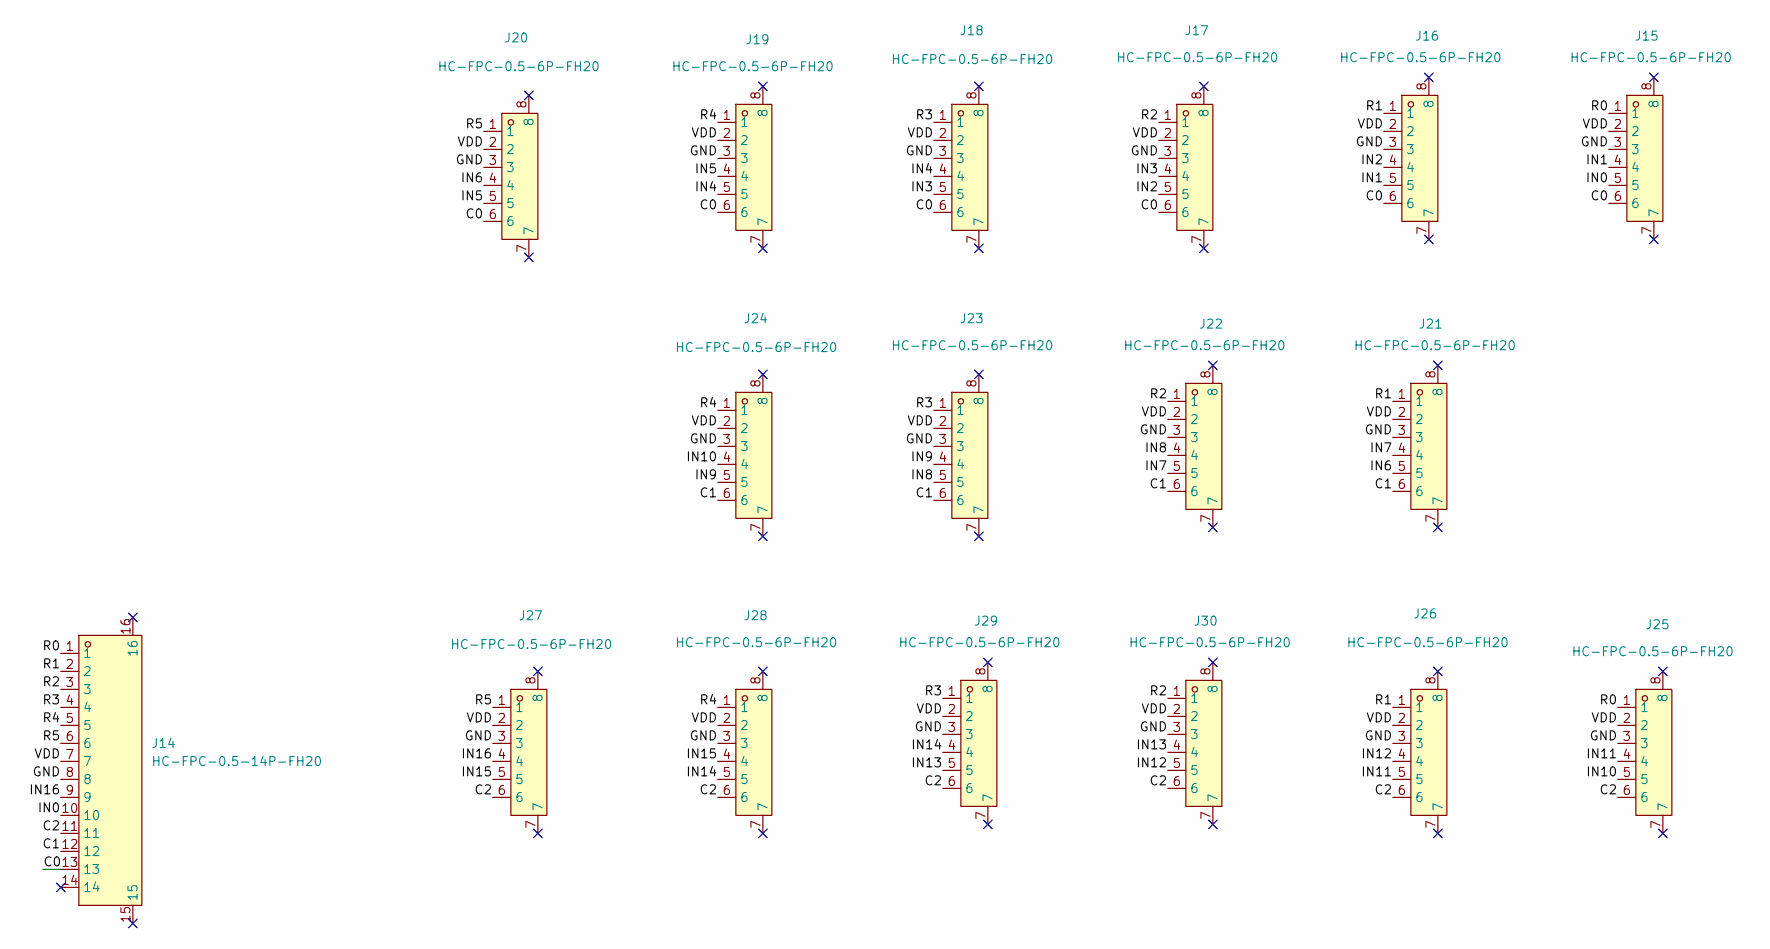
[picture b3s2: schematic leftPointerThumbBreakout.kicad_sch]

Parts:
J14: HC-FPC-0.5-14P-FH20; FPC-SMD_14P-P0.50_HC-FPC-0.5-14P-FH20; MPN HC-FPC-0.5-14P-FH20; LCSC Part C19273929
J15, J16, J17, J18, J19, J20, J21, J22, J23, J24, J25, J26, J27, J28, J29, J30: HC-FPC-0.5-6P-FH20; FPC-SMD_6P-P0.50_HC-FPC-0.5-6P-FH20; MPN HC-FPC-0.5-6P-FH20; LCSC Part C19273925

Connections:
/leftPointerThumbBreakout/C0: J14.13, J15.6, J16.6, J17.6, J18.6, J19.6, J20.6
/leftPointerThumbBreakout/C1: J14.12, J21.6, J22.6, J23.6, J24.6
/leftPointerThumbBreakout/C2: J14.11, J25.6, J26.6, J27.6, J28.6, J29.6, J30.6
/leftPointerThumbBreakout/GND: J14.8, J15.3, J16.3, J17.3, J18.3, J19.3, J20.3, J21.3, J22.3, J23.3, J24.3, J25.3, J26.3, J27.3, J28.3, J29.3, J30.3
/leftPointerThumbBreakout/IN0: J14.10, J15.5
/leftPointerThumbBreakout/IN1: J15.4, J16.5
/leftPointerThumbBreakout/IN2: J16.4, J17.5
/leftPointerThumbBreakout/IN3: J17.4, J18.5
/leftPointerThumbBreakout/IN4: J18.4, J19.5
/leftPointerThumbBreakout/IN5: J19.4, J20.5
/leftPointerThumbBreakout/IN6: J20.4, J21.5
/leftPointerThumbBreakout/IN7: J21.4, J22.5
/leftPointerThumbBreakout/IN8: J22.4, J23.5
/leftPointerThumbBreakout/IN9: J23.4, J24.5
/leftPointerThumbBreakout/IN10: J24.4, J25.5
/leftPointerThumbBreakout/IN11: J25.4, J26.5
/leftPointerThumbBreakout/IN12: J26.4, J30.5
/leftPointerThumbBreakout/IN13: J29.5, J30.4
/leftPointerThumbBreakout/IN14: J28.5, J29.4
/leftPointerThumbBreakout/IN15: J27.5, J28.4
/leftPointerThumbBreakout/IN16: J14.9, J27.4
/leftPointerThumbBreakout/R0: J14.1, J15.1, J25.1
/leftPointerThumbBreakout/R1: J14.2, J16.1, J21.1, J26.1
/leftPointerThumbBreakout/R2: J14.3, J17.1, J22.1, J30.1
/leftPointerThumbBreakout/R3: J14.4, J18.1, J23.1, J29.1
/leftPointerThumbBreakout/R4: J14.5, J19.1, J24.1, J28.1
/leftPointerThumbBreakout/R5: J14.6, J20.1, J27.1
/leftPointerThumbBreakout/VDD: J14.7, J15.2, J16.2, J17.2, J18.2, J19.2, J20.2, J21.2, J22.2, J23.2, J24.2, J25.2, J26.2, J27.2, J28.2, J29.2, J30.2
